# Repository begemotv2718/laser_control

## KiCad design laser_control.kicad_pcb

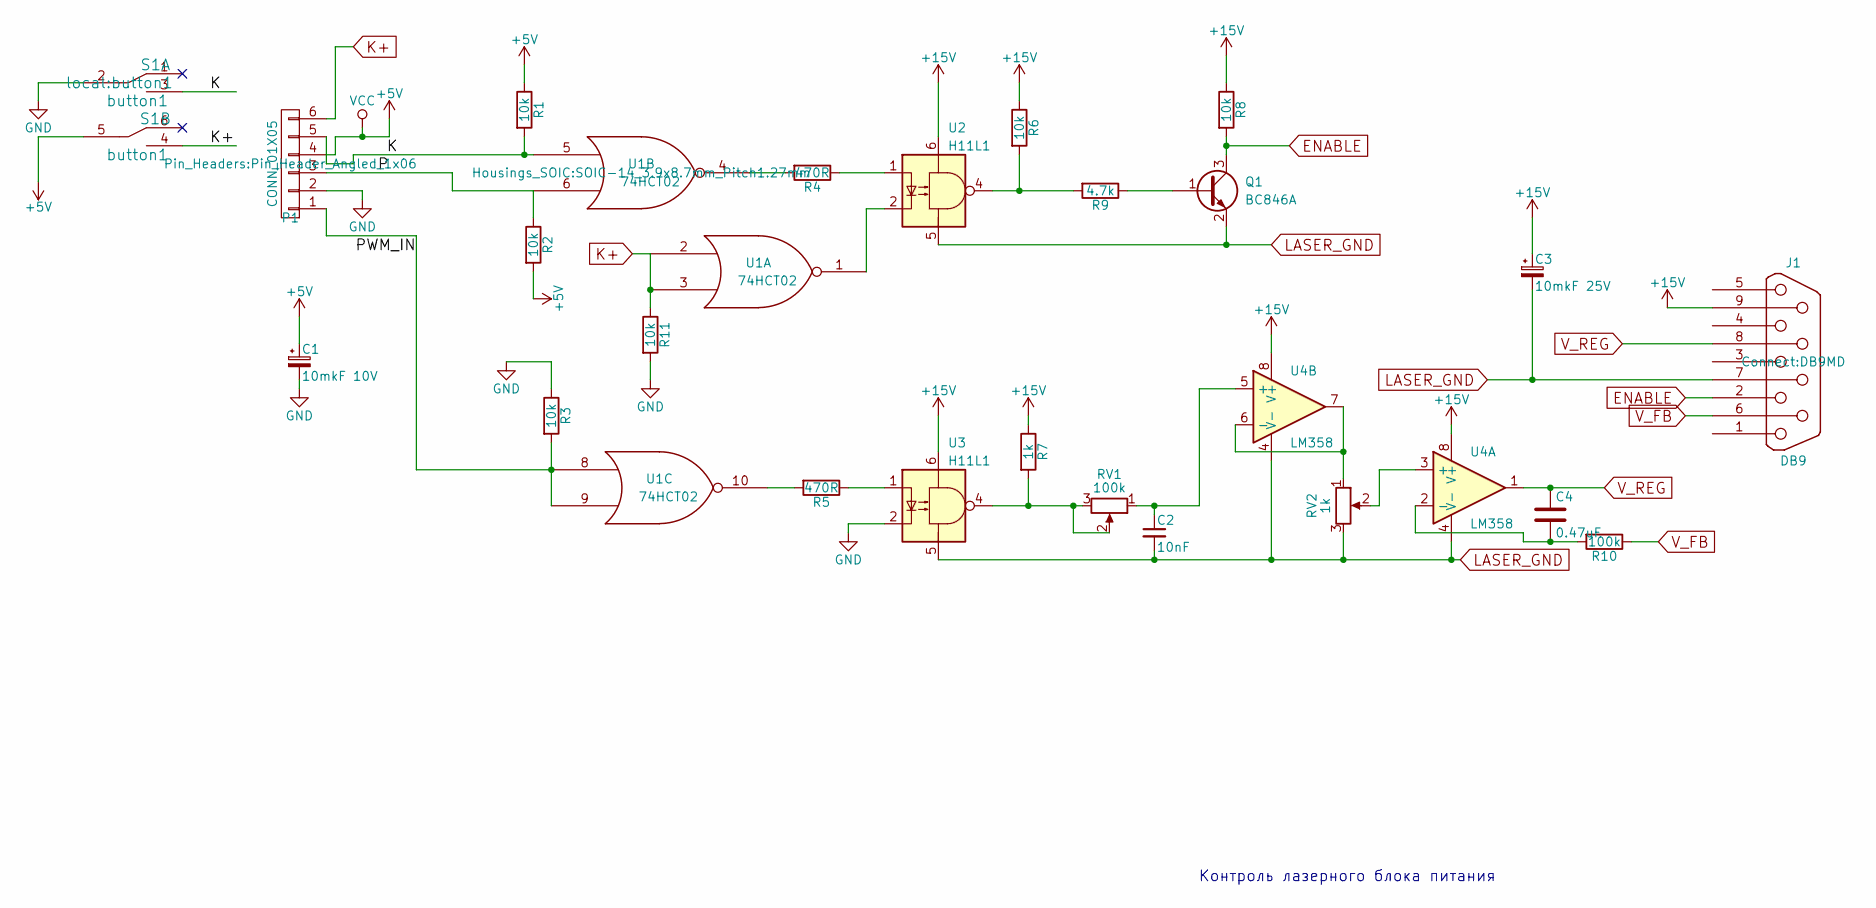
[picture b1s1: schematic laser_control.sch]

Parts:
C1: 10mkF 10V; c_elec_6.3x5.3
C2: 10nF; C_Disc_D6_P5
C3: 10mkF 25V; c_elec_6.3x5.3
C4: 0.47uF; C_0805_HandSoldering
J1: DB9; DB9MD
P1: CONN_01X05; Pin_Header_Angled_1x06
Q1: BC846A; SOT-23
R1, R2, R3: 10k; R_0805_HandSoldering
R4, R5: 470R; R_0805_HandSoldering
R6, R8, R11: 10k; Resistor_Horizontal_RM10mm
R7: 1k; R_0805_HandSoldering
R9: 4.7k; R_0805_HandSoldering
R10: 100k; Resistor_Horizontal_RM10mm
RV1: 100k; Potentiometer_Bourns_3296W_3-8Zoll_Inline_ScrewUp
RV2: 1k; Potentiometer_Bourns_3296W_3-8Zoll_Inline_ScrewUp
S1: button1
U1: 74HCT02; SOIC-14_3.9x8.7mm_Pitch1.27mm
U2, U3: H11L1; SO6-2.54
U4: LM358; SOIC-8_3.9x4.9mm_Pitch1.27mm

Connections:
+5V: C1.1, P1.4, R1.1, R2.2, S1.5, U1.14 (VCC)
+15V: C3.1, J1.9, R6.1, R7.1, R8.1, U2.6, U3.6, U4.8 (V+)
/K: P1.5, R1.2, S1.3, U1.5
/P: P1.3, R2.1, U1.6
/PWM_IN: P1.1, R3.2, U1.8, U1.9
ENABLE: J1.2, Q1.3 (C), R8.2
GND: C1.2, P1.2, R3.1, R11.2, S1.2, U1.7 (GND), U3.2
K+: P1.6, R11.1, S1.4, U1.2, U1.3
LASER_GND: C2.2, C3.2, J1.7, Q1.2 (E), RV2.3, U2.5, U3.5, U4.4 (V-)
unnamed: C2.1, RV1.1, U4.5 (+)
unnamed: C4.2, R10.2, U4.2 (-)
unnamed: Q1.1 (B), R9.1
unnamed: R4.1, U2.1
unnamed: R4.2, U1.4
unnamed: R5.1, U3.1
unnamed: R5.2, U1.10
unnamed: R6.2, R9.2, U2.4
unnamed: R7.2, RV1.2, RV1.3, U3.4
unnamed: RV2.1, U4.6 (-), U4.7
unnamed: RV2.2, U4.3 (+)
unnamed: U1.1, U2.2
V_FB: J1.6, R10.1
V_REG: C4.1, J1.8, U4.1

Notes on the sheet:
Контроль лазерного блока питания

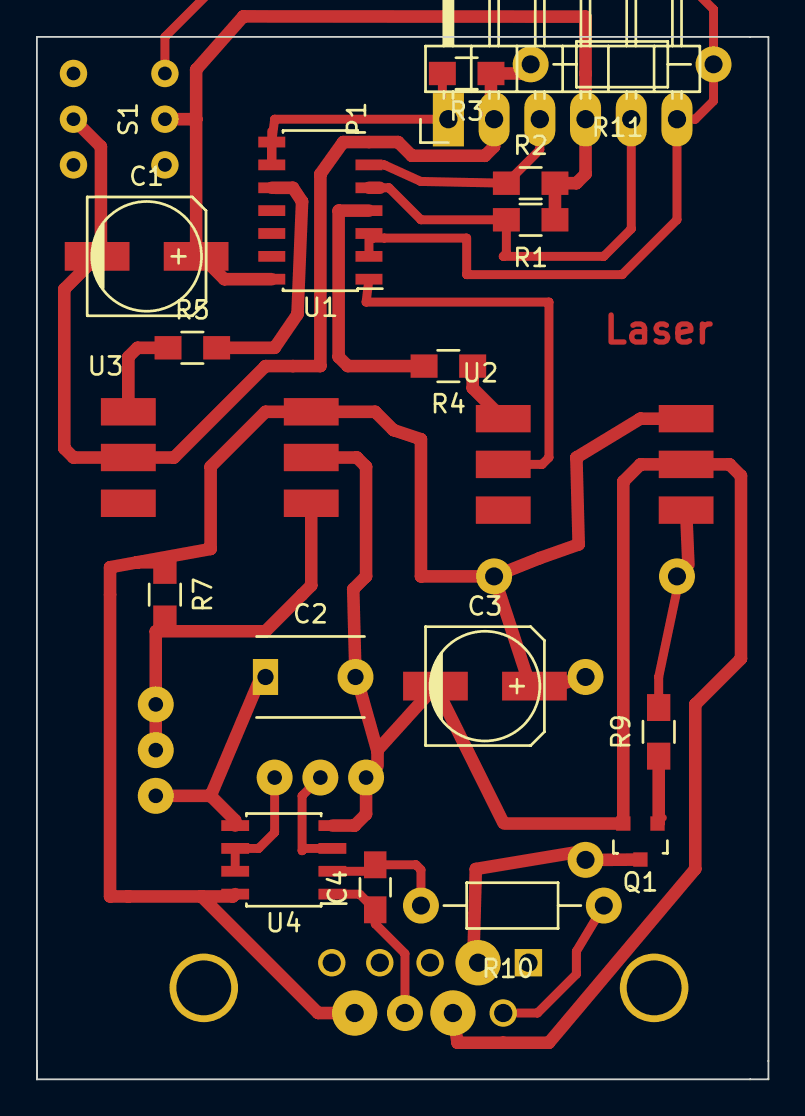
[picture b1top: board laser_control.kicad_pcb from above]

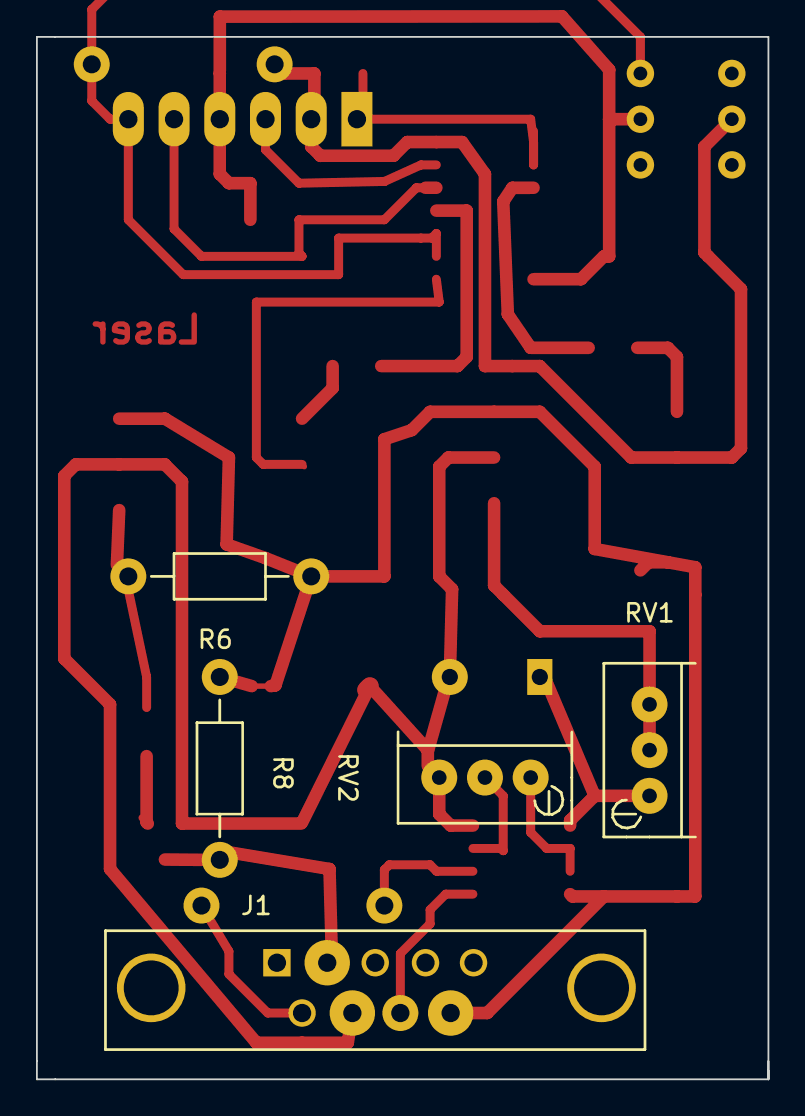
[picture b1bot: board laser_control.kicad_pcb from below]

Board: 2 copper layers, 40.6 x 57.9 mm, 25 parts (5 on the bottom side), 23 nets.

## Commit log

2018-12-16 Initial revision
2018-12-29 Minimal viable modifications
2020-08-08 Control with feedback
2020-08-08 Kicad 5 updates
